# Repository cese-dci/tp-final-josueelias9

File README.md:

## Trabajo práctico final de la asignatura DCI ##
Este repositorio contiene el trabajo práctico final para la asignatura de Diseño de Circuitos Impresos de la carrera de posgrado de FIUBA.

* Autor: Josué Elías Huamán Gonzales
* Título corto del trabajo:  XXXXCOMPLETARXXXX
* Descripción:  XXXXCOMPLETARXXXX

## Licencia de este trabajo ##
XXXMENCIONAR ACÁ LA LICENCIAXXX (Editar este párrafo) 
Y además colcar el archivo de texto de la misma en el directorio raíz.
Para este TP se pide que la licencia sea de hardware abierto.
Ver la sección "What license should I use?": https://www.oshwa.org/faq/

## Estructura del TP FINAL ##

Se propone y se pide utilizar la siguiente estructura.

* doc: Toda la información sobre el circuito, principalmente de autoría o procesamiento propio. Por ejemplo:
  * Notas de ingeniería propias.
  * Notas de aplicación propias.
  * Estudios previos, estado del arte, resumen de las investigaciones.
  * Notas con cálculos.
  * Dibujos adicionales.
  * Fotos de los prototipos.
  * Presupuestos, cotizaciones.
* info: Toda la iformación recolectada, principalmente de terceros, como por ejemplo:
  * Hojas de datos.
  * Notas de aplicación.
  * Info de productos comerciales.
  * Info en internet.
* pcb: Archivos de diseño esquemático y pcb.

Dependiendo la magnitud del proyecto, tendremos más o menos información en estos directorios. 
Revisar los README.md en cada directorio para conocer las pautas de cada uno para este TP.

NOTA: El alumno puede y debe borrar de este archivo todo lo que considere necesario, por ejemplo las aclaraciones del docente y esta misma nota.

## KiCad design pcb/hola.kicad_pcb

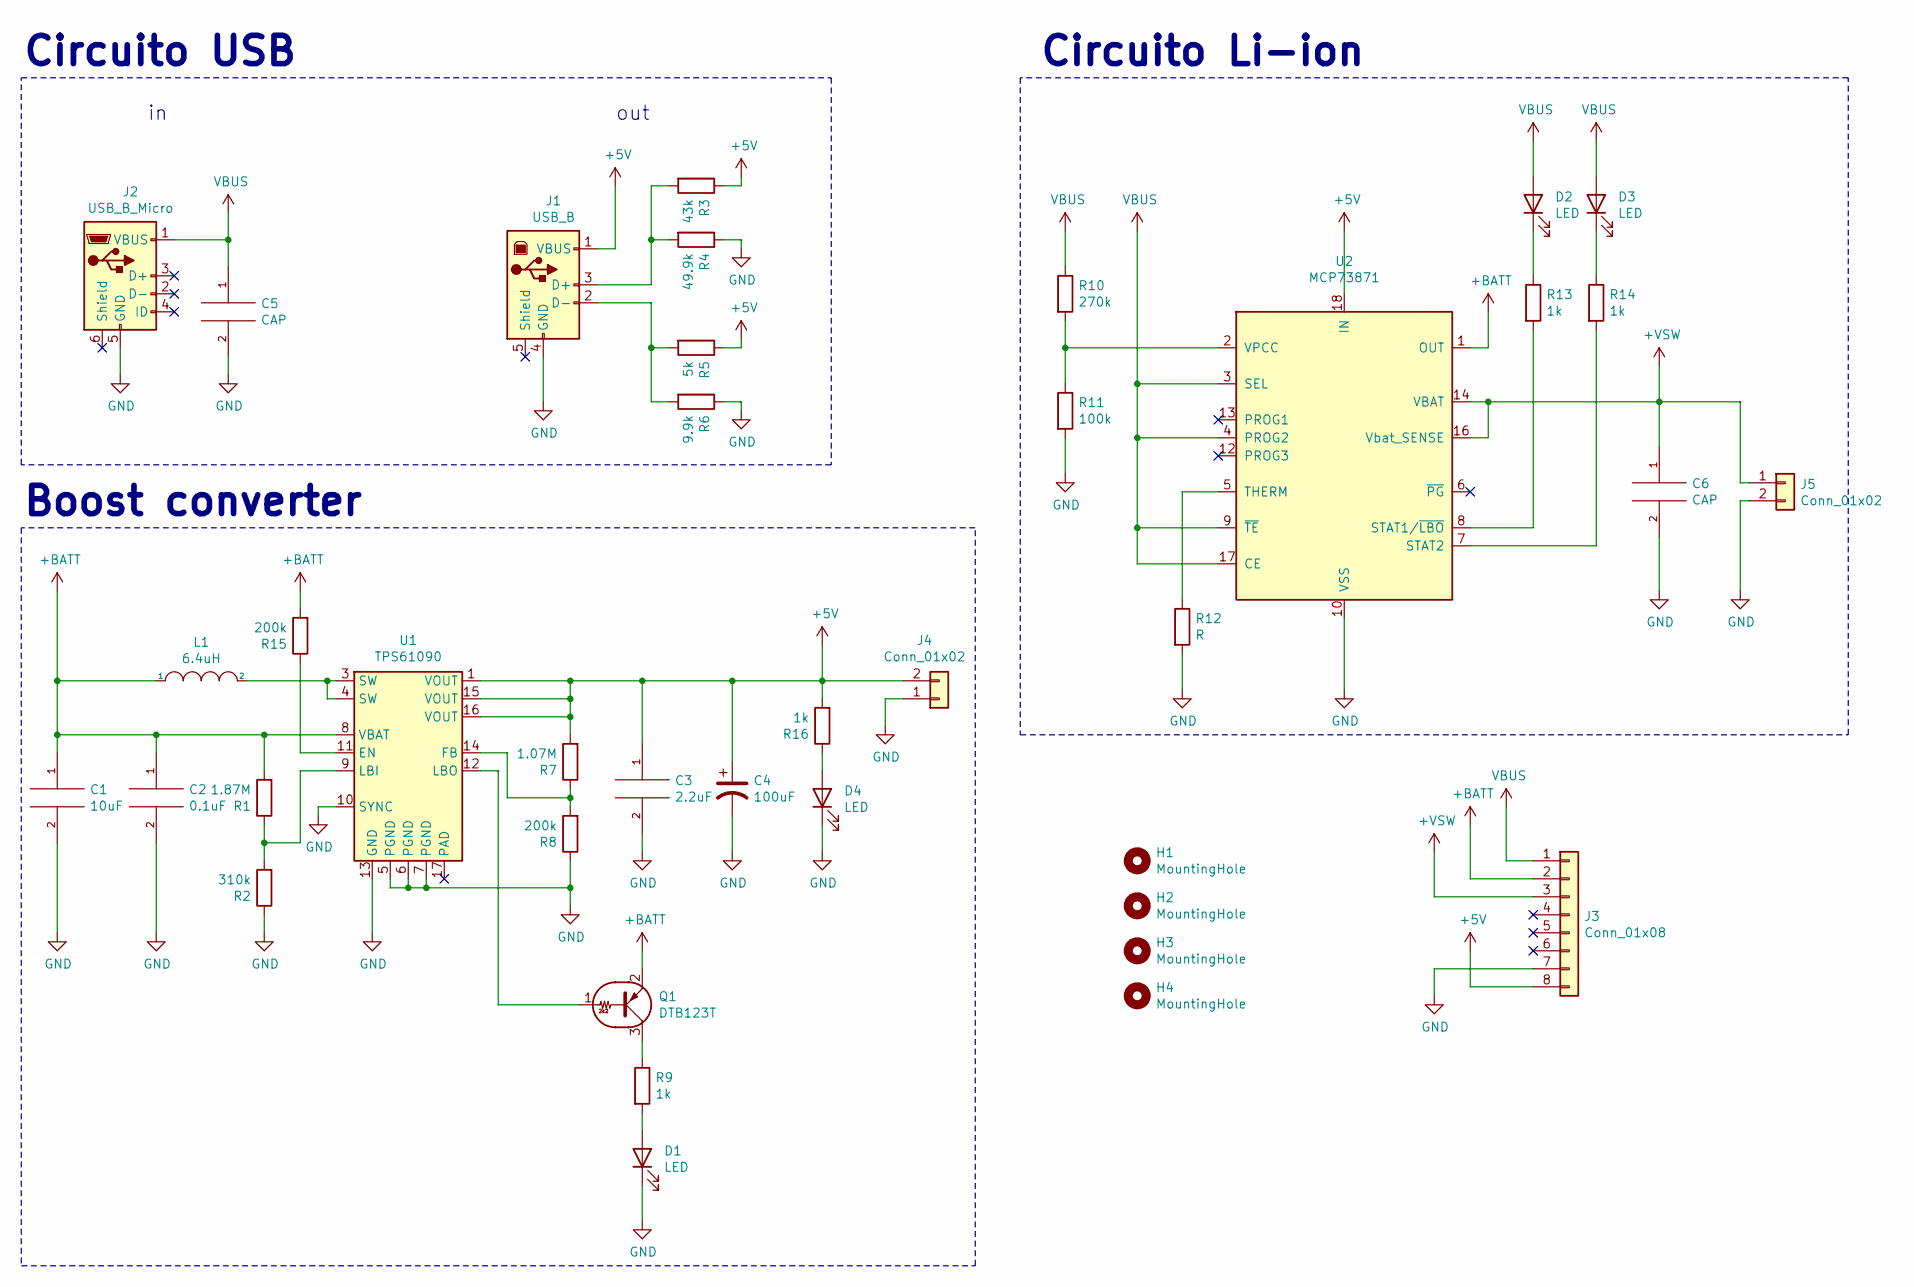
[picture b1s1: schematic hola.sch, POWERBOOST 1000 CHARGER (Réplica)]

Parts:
C1: 10uF; C_0402_1005Metric_Pad0.74x0.62mm_HandSolder
C2: 0.1uF; C_0402_1005Metric_Pad0.74x0.62mm_HandSolder
C3: 2.2uF; C_0402_1005Metric_Pad0.74x0.62mm_HandSolder
C4: 100uF; C_0402_1005Metric_Pad0.74x0.62mm_HandSolder
C5, C6: CAP; C_0402_1005Metric_Pad0.74x0.62mm_HandSolder
D1, D2, D3, D4: LED; LED_2010_5025Metric_Castellated
H1, H2, H3, H4: MountingHole; MountingHole_2.1mm
J1: USB_B; USB_B_Amphenol_MUSB-D511_Vertical_Rugged
J2: USB_B_Micro; USB_Micro-B_Amphenol_10103594-0001LF_Horizontal
J3: Conn_01x08; Hirose_DF13-08P-1.25DSA_1x08_P1.25mm_Vertical
J4: Conn_01x02; JWT_A3963_1x02_P3.96mm_Vertical
J5: Conn_01x02; JST_PH_S2B-PH-K_1x02_P2.00mm_Horizontal
L1: 6.4uH; L_1806_4516Metric
Q1: DTB123T; SOT-23_Handsoldering
R1: 1.87M; R_1206_3216Metric
R2: 310k; R_1206_3216Metric
R3: 43k; R_1206_3216Metric
R4: 49.9k; R_1206_3216Metric
R5: 5k; R_1206_3216Metric
R6: 9.9k; R_1206_3216Metric
R7: 1.07M; R_1206_3216Metric
R8, R15: 200k; R_1206_3216Metric
R9, R13, R14, R16: 1k; R_1206_3216Metric
R10: 270k; R_1206_3216Metric
R11: 100k; R_1206_3216Metric
R12: R; R_1206_3216Metric
U1: TPS61090; Texas_S-PVQFN-N16_EP2.7x2.7mm_ThermalVias
U2: MCP73871; QFN-20-1EP_4x4mm_P0.5mm_EP2.5x2.5mm

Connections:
+5V: C3.1, C4.1, J1.1 (VBUS), J3.8, J4.2, R3.1, R5.1, R7.2, R16.2, U1.1 (VOUT), U1.15 (VOUT), U1.16 (VOUT), U2.18 (IN), U2.19 (IN)
+BATT: C1.1, C2.1, J3.2, L1.1, Q1.2 (E), R1.2, R15.2, U1.8 (VBAT), U2.1 (OUT), U2.20 (OUT)
+VSW: C6.1, J3.3, J5.1, U2.14 (VBAT), U2.15 (VBAT), U2.16 (Vbat_SENSE)
GND: C1.2, C2.2, C3.2, C4.2, C5.2, C6.2, D1.1 (K), D4.1 (K), J1.4 (GND), J2.5 (GND), J3.7, J4.1, J5.2, R2.1, R4.1, R6.1, R8.1, R11.2, R12.2, U1.5 (PGND), U1.6 (PGND), U1.7 (PGND), U1.10 (SYNC), U1.13 (GND), U2.10 (VSS), U2.11 (VSS), U2.21 (VSS)
unnamed: D1.2 (A), R9.2
unnamed: D2.1 (K), R13.1
unnamed: D3.1 (K), R14.1
unnamed: D4.2 (A), R16.1
unnamed: J1.2 (D-), R5.2, R6.2
unnamed: J1.3 (D+), R3.2, R4.2
unnamed: L1.2, U1.3 (SW), U1.4 (SW)
unnamed: Q1.1 (B), U1.12 (LBO)
unnamed: Q1.3 (C), R9.1
unnamed: R1.1, R2.2, U1.9 (LBI)
unnamed: R7.1, R8.2, U1.14 (FB)
unnamed: R10.2, R11.1, U2.2 (VPCC)
unnamed: R12.1, U2.5 (THERM)
unnamed: R13.2, U2.8 (STAT1/~LBO~)
unnamed: R14.2, U2.7 (STAT2)
unnamed: R15.1, U1.11 (EN)
VBUS: C5.1, D2.2 (A), D3.2 (A), J2.1 (VBUS), J3.1, R10.1, U2.3 (SEL), U2.4 (PROG2), U2.9 (~TE), U2.17 (CE)

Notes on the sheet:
Circuito Li-ion
Circuito USB
Boost converter
out

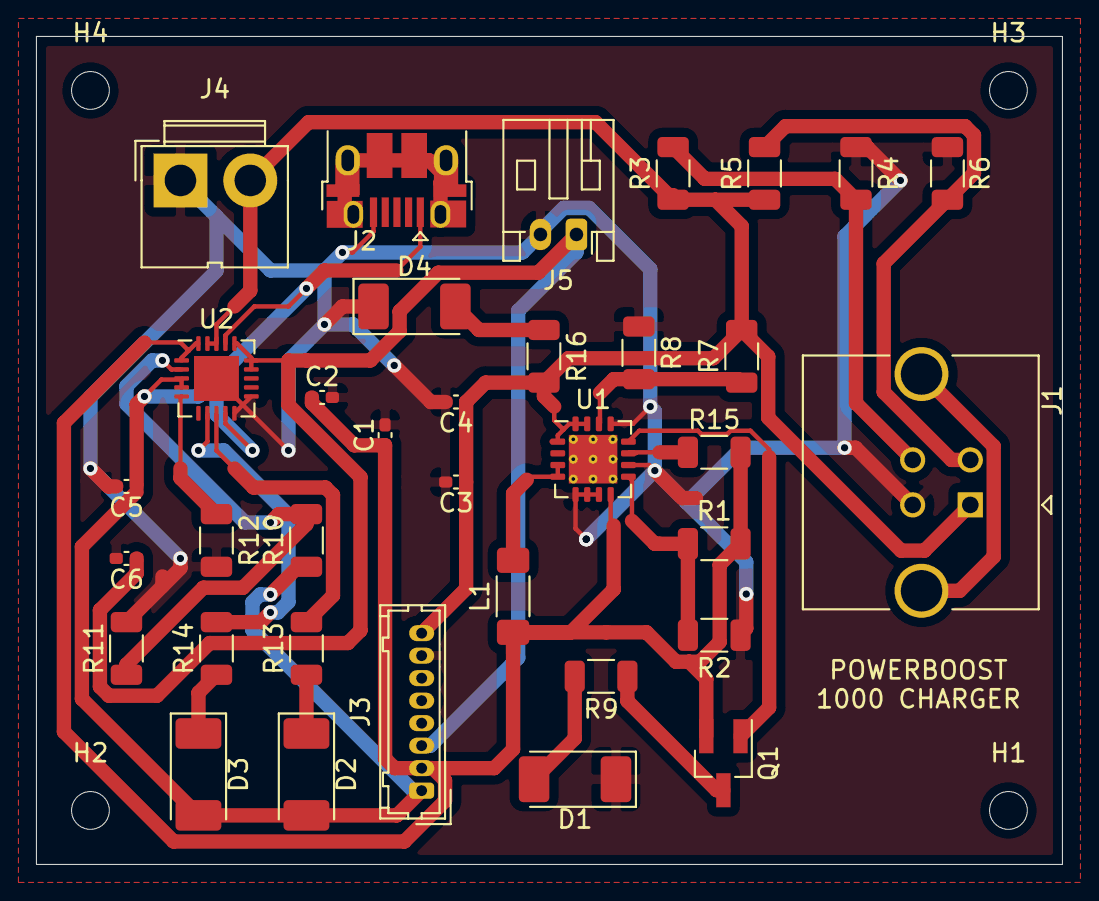
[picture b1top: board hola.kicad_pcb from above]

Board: 2 copper layers, 57.0 x 46.0 mm, 39 parts (0 on the bottom side), 21 nets.

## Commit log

2021-09-16 avance
2021-09-23 avance 23-09-2021
2021-10-18 TP Final
2021-10-20 actualizacion
